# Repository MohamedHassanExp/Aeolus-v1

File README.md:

# Aeolus-V1 IoT Development Board

A custom-designed, compact ESP32-based IoT development board featuring integrated power management and sensor interfaces, complete with full schematic capture, layout, and manufacturing-ready fabrication files.

##  Table of Contents
- [About the Project](#about-the-project)
- [Tech Stack](#tech-stack)
- [Getting Started](#getting-started)
- [Repository Structure](#repository-structure)

##  About the Project

This project contains the complete hardware design files for the Aeolus-V1. Designed as a compact Internet of Things (IoT) development platform, it leverages the ESP32 microcontroller and incorporates built-in power management alongside versatile sensor interfaces to streamline the prototyping of connected wireless devices.

### Tech Stack
*   **EDA Software:** KiCad (for schematic capture and PCB layout)
*   **Hardware Type:** ESP32 Microcontroller

##  Getting Started

Follow these instructions to view or modify the hardware design files locally.

### Prerequisites

*   [KiCad EDA](https://www.kicad.org/download/) to open the core project files.
*   A PDF viewer to read the exported schematics.
*   A Gerber viewer (if you only want to inspect the manufacturing layers).

### Installation

1. Clone the repository:
   ```bash
   git clone https://github.com/MohamedHassanExp/Aeolus-v1.git
2. Navigate to the project directory
   ```bash
   cd Aeolus-v1-main
3. Open `Aeolus-v1.kicad_pro` project file using KiCad.

## Repository Structure

The repository is organized to separate the editable design files from the static manufacturing outputs:

*   **Design Files:**
     The root directory contains the core KiCad project files, including the schematic (Aeolus-v1.kicad_sch), the physical layout (Aeolus-v1.kicad_pcb), and a PDF export of the design (Aeolus-v1.pdf).
*    **Board Renders:**
      High-resolution 3D renders of the physical layout are available as **Aeolus-V1-PCB Isometric.png** and **Aeolus-V1-PCB top.png**.  
*    **Manufacturing Files (Manufacturing/):** 
      This directory contains everything a fabrication house like JLCPCB or PCBWay needs to manufacture and assemble the board:
      * **Aeolus-v1-gerber.rar:** The compressed Gerber layers and drill files for PCB fabrication.
      * **Aeolus-v1-BOM.csv:** The complete Bill of Materials for component sourcing and assembly.
      * **Aeolus-V1-bottom-pos.csv** and **Aeolus-V1-top-pos.csv** The centroid/pick-and-place data for automated SMD assembly.

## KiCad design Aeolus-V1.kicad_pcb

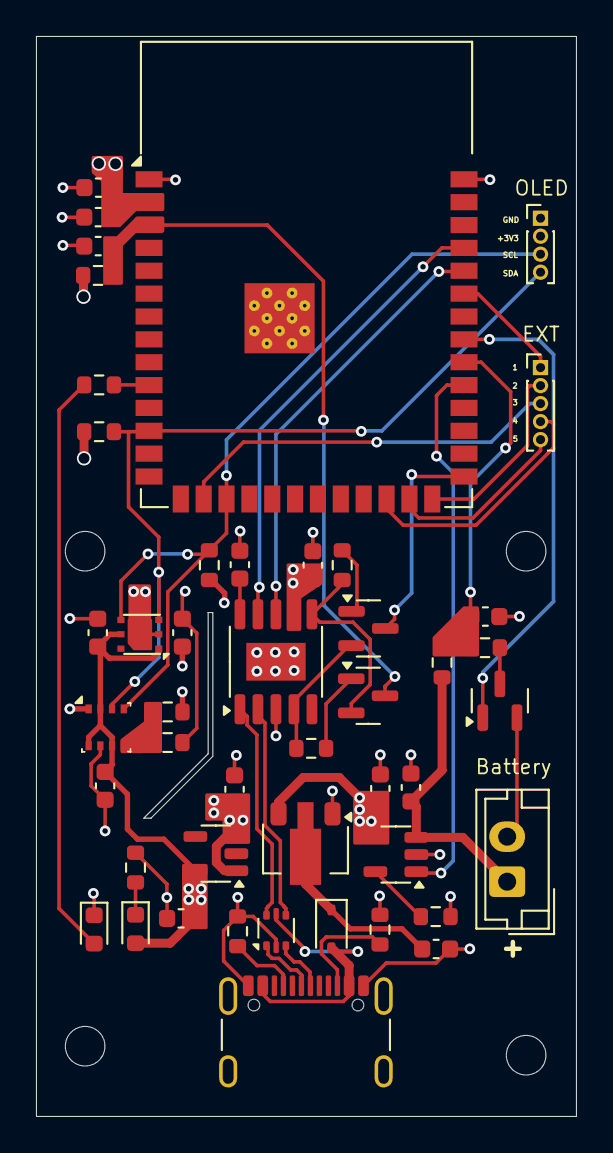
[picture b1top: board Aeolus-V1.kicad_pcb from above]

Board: 4 copper layers, 30.0 x 60.0 mm, 46 parts (0 on the bottom side), 37 nets.

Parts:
C1, C6, C7, C10, C12, C13, C14: 0u1; C_0603_1608Metric
C2, C5, C9, C11: 1u; C_0603_1608Metric
C3, C4: 4u7; C_0603_1608Metric
C8: 10u; C_0603_1608Metric
D1: 1N5819WS; D_SOD-323
D2: LED_GREEN; LED_0603_1608Metric
D5: GREEN; LED_0603_1608Metric
J1: BATTERY; JST_EH_B2B-EH-A_1x02_P2.50mm_Vertical
J2: USB_C_Receptacle_USB2.0_14P; USB_C_Receptacle_GCT_USB4105-xx-A_16P_TopMnt_Horizontal
J3: EXT; PinHeader_1x05_P1.00mm_Vertical
J4: OLED_I2C; PinHeader_1x04_P1.00mm_Vertical
Q1, Q4: BC818; SOT-23
Q3: 2N7002H; SOT-23
R1, R4, R5: 10k; R_0603_1608Metric
R2, R13: 5k1; R_0603_1608Metric
R3: 2k; R_0603_1608Metric
R6, R7: 0; R_0603_1608Metric
R8, R9: 4k7; R_0603_1608Metric
R10: 1.5k; R_0603_1608Metric
R11, R12: 100k; R_0603_1608Metric
R14: 1k; R_0603_1608Metric
U1: ESP32-S3-WROOM-1
U2: BME280; Bosch_LGA-8_2.5x2.5mm_P0.65mm_ClockwisePinNumbering
U3: MCP73831-2-OT; SOT-23-5
U4: AP2112K-3.3; SOT-23-5
U5: CH340K; SSOP-10-1EP_3.9x4.9mm_P1mm_EP2.1x3.3mm
U6: SGP40; DFN-6
U7: USBLC6-2P6; SOT-666
U8: LP5300; SOT-89-3

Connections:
+3.3V: C7.1, C8.1, C9.2, C10.1, C11.1, C12.1, D5.2 (A), J4.2, R1.1, R6.1, R8.2, R9.2, U1.2 (3V3), U2.2 (CSB), U2.6 (VDDIO), U2.8 (VDD), U4.5 (VOUT), U6.1 (VDD), U6.5 (VDDH)
+5V: C2.2, C3.2, C13.1, U3.4 (V_{DD}), U4.1 (VIN), U4.3 (EN), U5.7 (VCC), U8.3 (V_{OUT})
/MCU and Connectors/USB_D+: J2.A6 (D+), U7.1 (I/O1)
/MCU and Connectors/USB_D-: J2.A7 (D-), U7.3 (I/O2)
BAT+: C4.2, J1.1, R11.1, U3.3 (V_{BAT})
BAT_GAUGE_EN: Q3.1 (G), U1.33 (IO40)
BAT_LVL: C14.1, R11.2, R12.1, U1.32 (IO39)
BAT_STAT: U1.31 (IO38), U3.1 (STAT)
CONV_RX: U1.37 (TXD0), U5.9 (RXD)
CONV_TX: U1.36 (RXD0), U5.8 (TXD)
D+: U5.1 (UD+), U7.6 (I/O1)
D-: U5.2 (UD-), U7.4 (I/O2)
DTR: Q1.2 (E), R4.1, U5.4 (~DTR)
EN: C1.1, Q4.3 (C), R1.2, U1.3 (EN)
EXT_1: J3.1, U1.35 (IO42)
EXT_2: J3.2, U1.26 (IO45)
EXT_3: J3.3, U1.16 (IO46)
EXT_4: J3.4, U1.24 (IO47)
EXT_5: J3.5, U1.25 (IO48)
GND: C1.2, C2.1, C3.1, C4.1, C5.1, C6.1, C7.2, C8.2, C9.1, C10.2, C11.2, C12.2, C13.2, C14.2, D2.1 (K), J1.2, J2.A1 (GND), J2.A12 (GND), J2.B1 (GND), J2.B12 (GND), J4.1, Q3.2 (S), R2.2, R3.2, R7.1, R10.2, R13.2, U1.1 (GND), U1.40 (GND), U1.41 (GND), U2.1 (GND), U2.7 (GND), U3.2 (V_{SS}), U4.2 (GND), U5.3 (GND), U5.11 (GND), U6.2 (VSS), U6.7 (PAD), U7.2 (GND), U8.1 (GND)
ID0: Q1.3 (C), U1.27 (IO0)
unnamed: D1.2 (A), J2.A4 (VBUS), J2.A9 (VBUS), J2.B4 (VBUS), J2.B9 (VBUS), U7.5 (VBUS)
unnamed: D2.2 (A), R14.2
unnamed: D5.1 (K), R10.1
unnamed: J2.A5 (CC1), R2.1
unnamed: J2.B5 (CC2), R13.1
unnamed: Q1.1 (B), R5.2
unnamed: Q3.3 (D), R12.2
unnamed: Q4.1 (B), R4.2
unnamed: R14.1, U1.10 (IO17)
unnamed: R6.2, R7.2, U2.5 (SDO)
unnamed: R3.1, U3.5 (PROG)
unnamed: C6.2, U5.10 (V3)
RST: Q4.2 (E), R5.1, U5.6 (~RTS)
SCL: J4.3, R9.1, U1.17 (IO9), U2.4 (SCK), U6.4 (SCL)
SDA: J4.4, R8.1, U1.12 (IO8), U2.3 (SDI), U6.3 (SDA)
USB_PWR: C5.2, D1.1 (K), U8.2 (V_{IN})

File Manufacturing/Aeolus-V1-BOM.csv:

"Id";"Designator";"Footprint";"Quantity";"Designation";"Supplier and ref";
1;"R4,R5,R1";"R_0603_1608Metric";3;"10k";;;
2;"J4";"PinHeader_1x04_P1.00mm_Vertical";1;"OLED_I2C";;;
3;"Q3";"SOT-23";1;"2N7002H";;;
4;"J3";"PinHeader_1x05_P1.00mm_Vertical";1;"EXT";;;
5;"D2";"LED_0603_1608Metric";1;"LED_GREEN";;;
6;"U6";"DFN-6";1;"SGP40";;;
7;"U8";"SOT-89-3";1;"LP5300";;;
8;"D1";"D_SOD-323";1;"1N5819WS";;;
9;"U1";"ESP32-S3-WROOM-1";1;"ESP32-S3-WROOM-1";;;
10;"R13,R2";"R_0603_1608Metric";2;"5k1";;;
11;"R3";"R_0603_1608Metric";1;"2k";;;
12;"C10,C12,C6,C14,C13,C7,C1";"C_0603_1608Metric";7;"0u1";;;
13;"R6,R7";"R_0603_1608Metric";2;"0";;;
14;"R12,R11";"R_0603_1608Metric";2;"100k";;;
15;"R14";"R_0603_1608Metric";1;"1k";;;
16;"Q4,Q1";"SOT-23";2;"BC818";;;
17;"C2,C11,C9,C5";"C_0603_1608Metric";4;"1u";;;
18;"R10";"R_0603_1608Metric";1;"1.5k";;;
19;"C3,C4";"C_0603_1608Metric";2;"4u7";;;
20;"U4";"SOT-23-5";1;"AP2112K-3.3";;;
21;"U5";"SSOP-10-1EP_3.9x4.9mm_P1mm_EP2.1x3.3mm";1;"CH340K";;;
22;"R8,R9";"R_0603_1608Metric";2;"4k7";;;
23;"U7";"SOT-666";1;"USBLC6-2P6";;;
24;"C8";"C_0603_1608Metric";1;"10u";;;
25;"U2";"Bosch_LGA-8_2.5x2.5mm_P0.65mm_ClockwisePinNumbering";1;"BME280";;;
26;"J1";"JST_EH_B2B-EH-A_1x02_P2.50mm_Vertical";1;"BATTERY";;;
27;"J2";"USB_C_Receptacle_GCT_USB4105-xx-A_16P_TopMnt_Horizontal";1;"USB_C_Receptacle_USB2.0_14P";;;
28;"U3";"SOT-23-5";1;"MCP73831-2-OT";;;
29;"D5";"LED_0603_1608Metric";1;"GREEN";;;

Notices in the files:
README.md:
License: MIT
